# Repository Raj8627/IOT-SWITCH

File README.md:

# IOT-SWITCH ESP8266
Eagle PCB
WIFI Touch Switch

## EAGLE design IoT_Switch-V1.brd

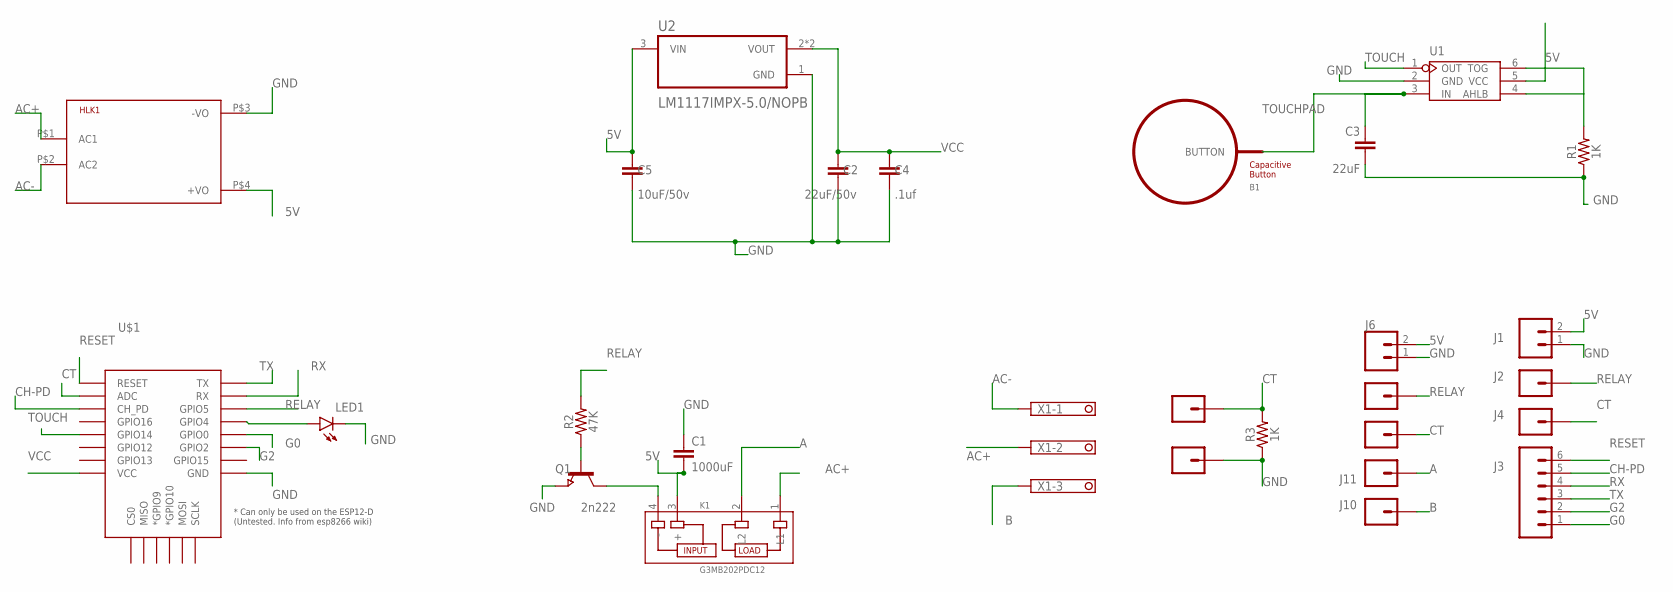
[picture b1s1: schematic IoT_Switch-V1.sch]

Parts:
B1: BUTTON_PASSIVE8MM; BUTTON_PASSIVE_8MM
C1: 1000uF; 0805
C2: 22uF/50v; 0805
C3: 22uF; 0805
C4: .1uf; 0805
C5: 10uF/50v; 0805
HLK1: HLK-PM013W; HLK-PM01
J1, J6: CONN_02; 1X02
J2, J4, J5, J7, J8, J9, J10, J11: CONN_01; 1X01
J3: CONN_06NO_SILK_FEMALE_PTH; 1X06_NO_SILK
K1: G3MB202PDC12; RELAY_G3MB202PDC12
LED1: LED1206; LED-1206
Q1: 2n222; SOT23
R1, R3: 1K; 0805
R2: 47K; 0805
U1: TTP223; SOT23-6L
U2: LM1117IMPX-5.0/NOPB; SOT230P700X180-4N
U$1: ESP12ESMD; ESP12E-SMD
X1: TERMINAL-BLOCK-3.5MM-3-PIN-ROUND-PAD; TERMINAL-BLOCK-3-PIN-3.5MM-ROUND-PAD

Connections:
5V: C1.2, C5.1, HLK1.P$4 (+VO), J1.2, J6.2, K1.3 (+), U1.5 (VCC), U2.3 (VIN)
A: J11.1, K1.2 (L2)
AC+: HLK1.P$1 (AC1), K1.1 (L1), X1.2
AC-: HLK1.P$2 (AC2), X1.1
B: J10.1, X1.3
CH-PD: J3.5, U$1.CH_PD
CT: J4.1, J7.1, J8.1, R3.2, U$1.ADC
G0: J3.1, U$1.GPIO0
G2: J3.2, U$1.GPIO2
GND: C1.1, C2.2, C3.2, C4.2, C5.2, HLK1.P$3 (-VO), J1.1, J6.1, J9.1, LED1.C, Q1.2 (E), R1.1, R3.1, U1.2 (GND), U2.1 (GND), U$1.GND
unnamed: LED1.A, U$1.GPIO4
unnamed: K1.4 (-), Q1.3 (C)
unnamed: Q1.1 (B), R2.1
unnamed: R1.2, U1.4 (AHLB), U1.6 (TOG)
RELAY: J2.1, J5.1, R2.2, U$1.GPIO5
RESET: J3.6, U$1.RESET
RX: J3.4, U$1.RXD0 (RX)
TOUCH: U1.1 (OUT), U$1.GPIO14
TOUCHPAD: B1.BUTTON, C3.1, U1.3 (IN)
TX: J3.3, U$1.TXD0 (TX)
VCC: C2.1, C4.1, U2.2 (VOUT), U2.4 (VOUT), U$1.VCC

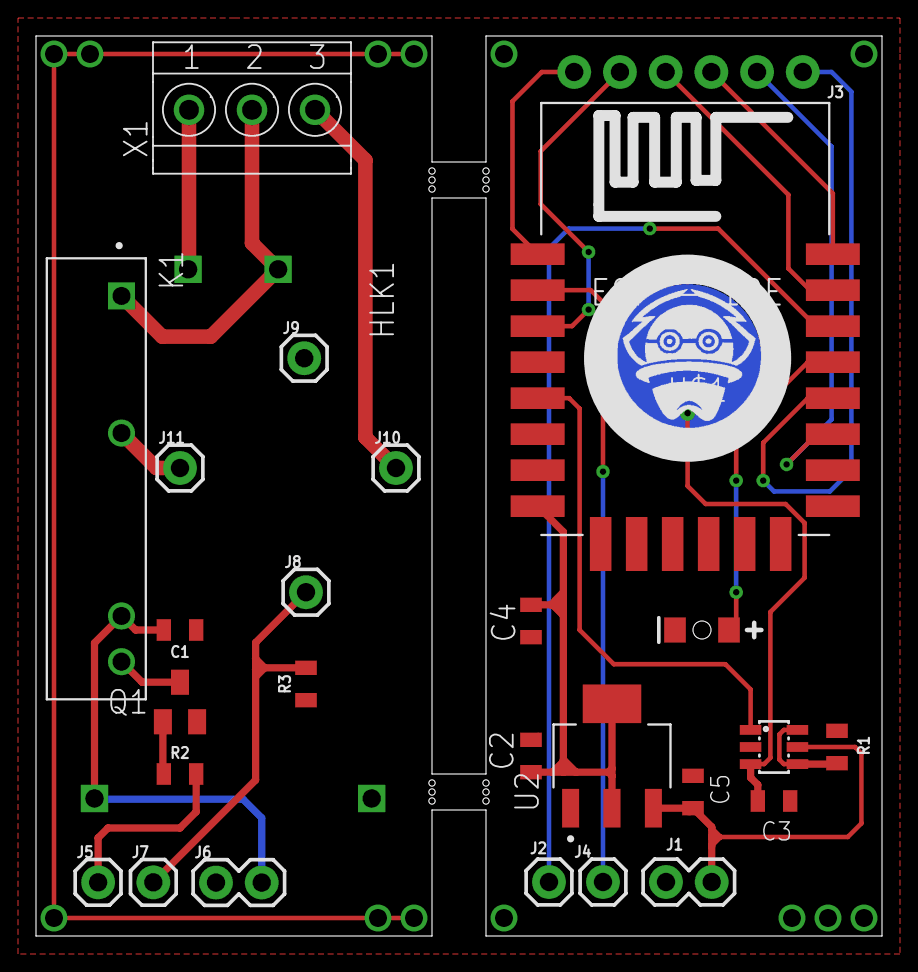
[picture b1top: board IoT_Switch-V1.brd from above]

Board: 2 copper layers, 47.0 x 50.0 mm, 28 parts (1 on the bottom side), 21 nets.

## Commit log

2021-07-15 brd file
2021-07-15 PCB v1

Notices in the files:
parts and their libraries:
SparkFun-Resistors: Licensing: Creative Commons ShareAlike 4.0 International - https://creativecommons.org/licenses/by-sa/4.0
PatternAgents-TouchWidgets: License : http://creativecommons.org/licenses/by-sa/4.0/ (Creative Commons 4.0)
